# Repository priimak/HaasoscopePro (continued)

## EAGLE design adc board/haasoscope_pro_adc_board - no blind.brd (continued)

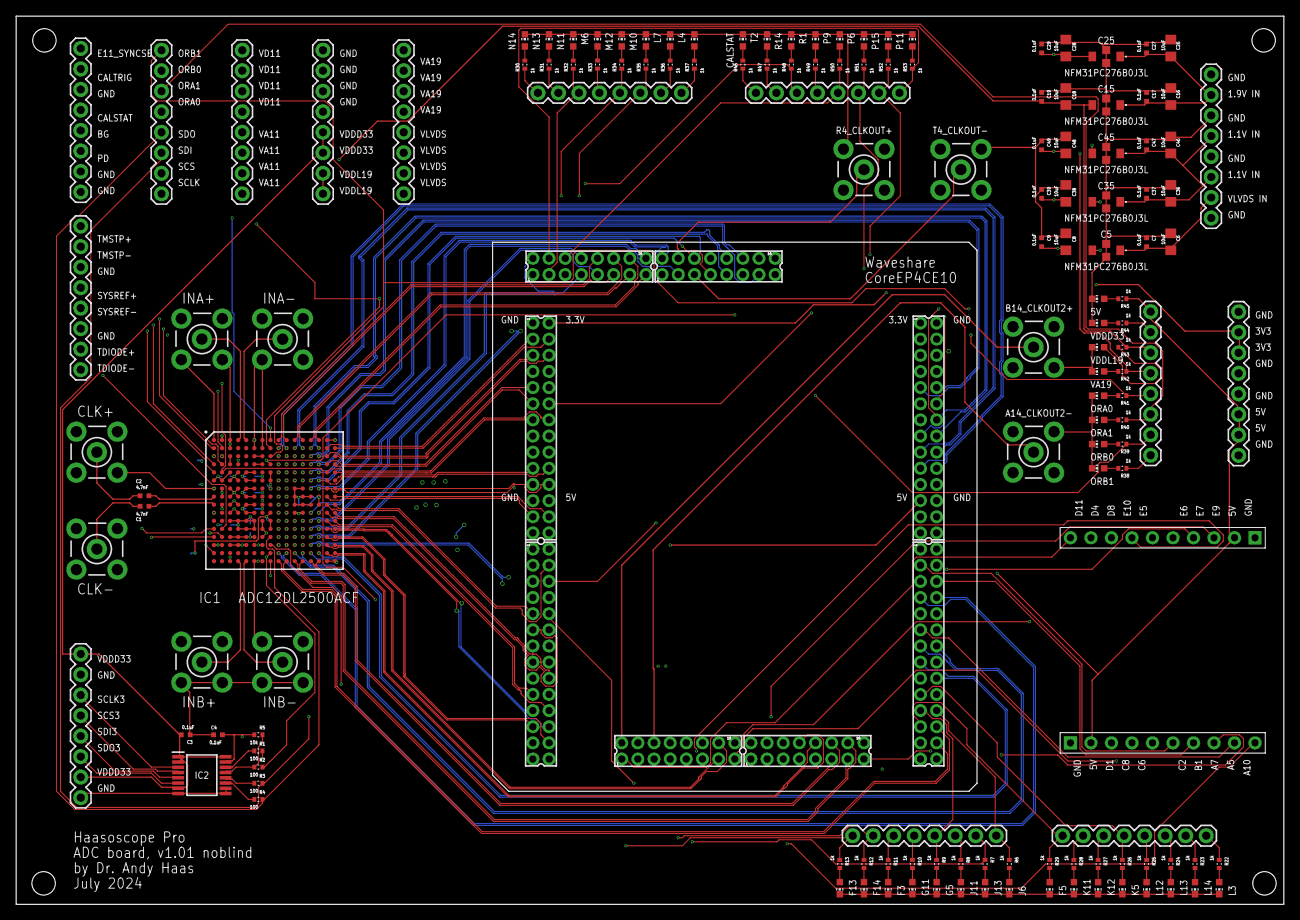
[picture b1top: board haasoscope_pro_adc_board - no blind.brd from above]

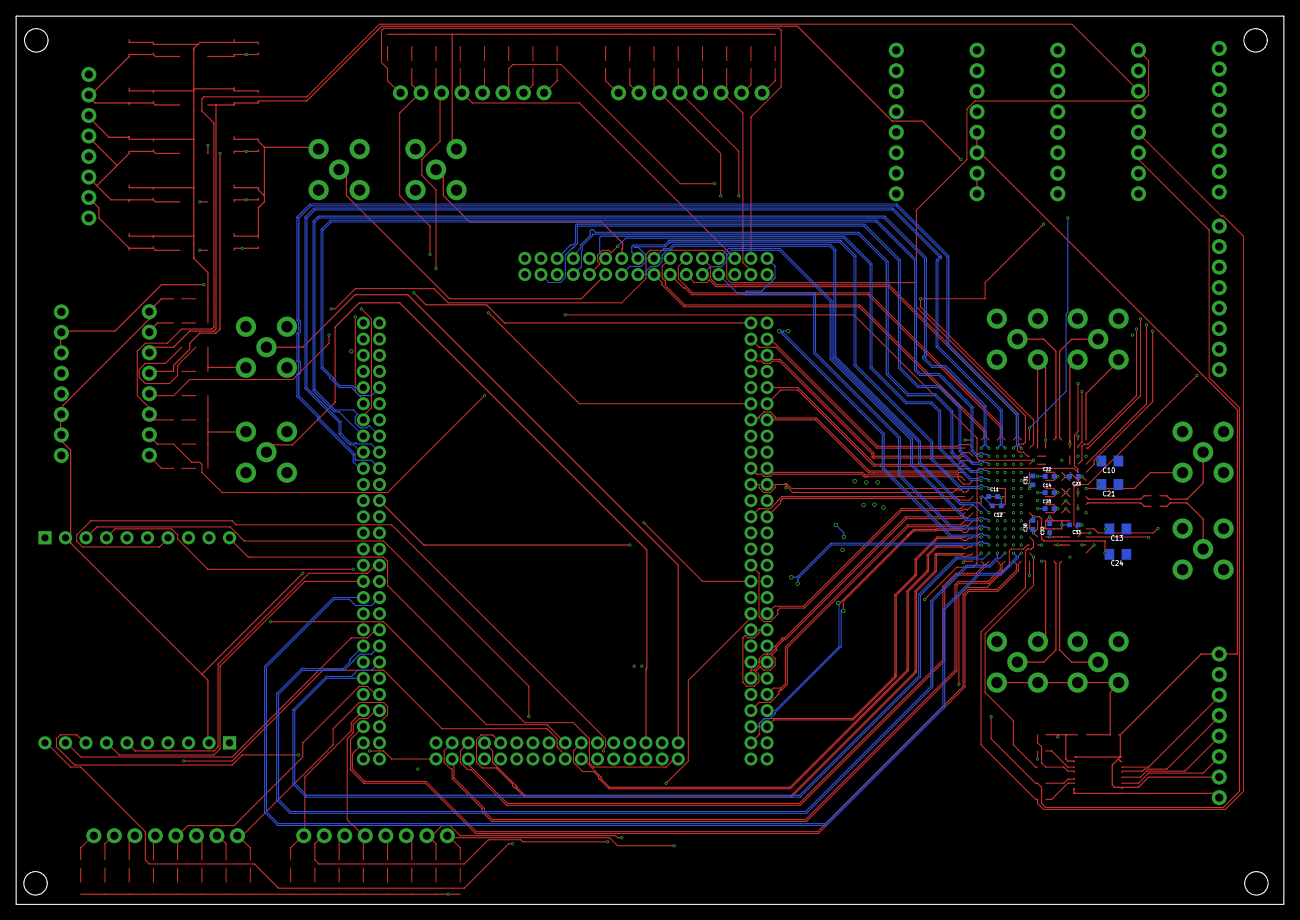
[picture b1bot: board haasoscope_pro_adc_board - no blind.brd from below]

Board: 10 copper layers, 157.0 x 110.0 mm, 164 parts (14 on the bottom side), 250 nets.

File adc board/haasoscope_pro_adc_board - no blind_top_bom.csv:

Comment,Designator,Footprint,LCSC Part #
0.1uF,C3 C4 C7 C9 C17 C19 C27 C29 C37 C39 C47 C49,RESC0402_N,
1k,R6 R7 R8 R9 R10 R11 R12 R13 R22 R23 R24 R25 R26 R27 R28 R29 R30 R31 R32 R33 R34 R35 R36 R37 R38 R39 R40 R41 R42 R43 R44 R45 R46 R47 R48 R49 R50 R51 R52 R53,RES-0402,
4.7nF,C1 C2,RESC0402_N,
10k,R5,RES-0402,
10uF,C6 C8 C16 C18 C26 C28 C36 C38 C46 C48,RESC0805_N,
100,R1 R2 R3 R4,RES-0402,
ADC12DL2500ACF,IC1,BGA256C100P16X16_1700X1700X331,
NFM31PC276B0J3L,C5 C15 C25 C35 C45,NFM31HK103R1H3L,
SN74AVC4T774PWR,IC2,SOP65P640X120-16N,
red,LED1 LED2 LED3 LED4 LED5 LED6 LED7 LED8 LED17 LED18 LED19 LED20 LED21 LED22 LED23 LED24 LED25 LED26 LED27 LED28 LED29 LED30 LED31 LED32 LED33 LED34 LED35 LED36 LED37 LED38 LED39 LED40 LED41 LED42 LED43 LED44 LED45 LED46 LED47 LED48,CHIP-LED0603,

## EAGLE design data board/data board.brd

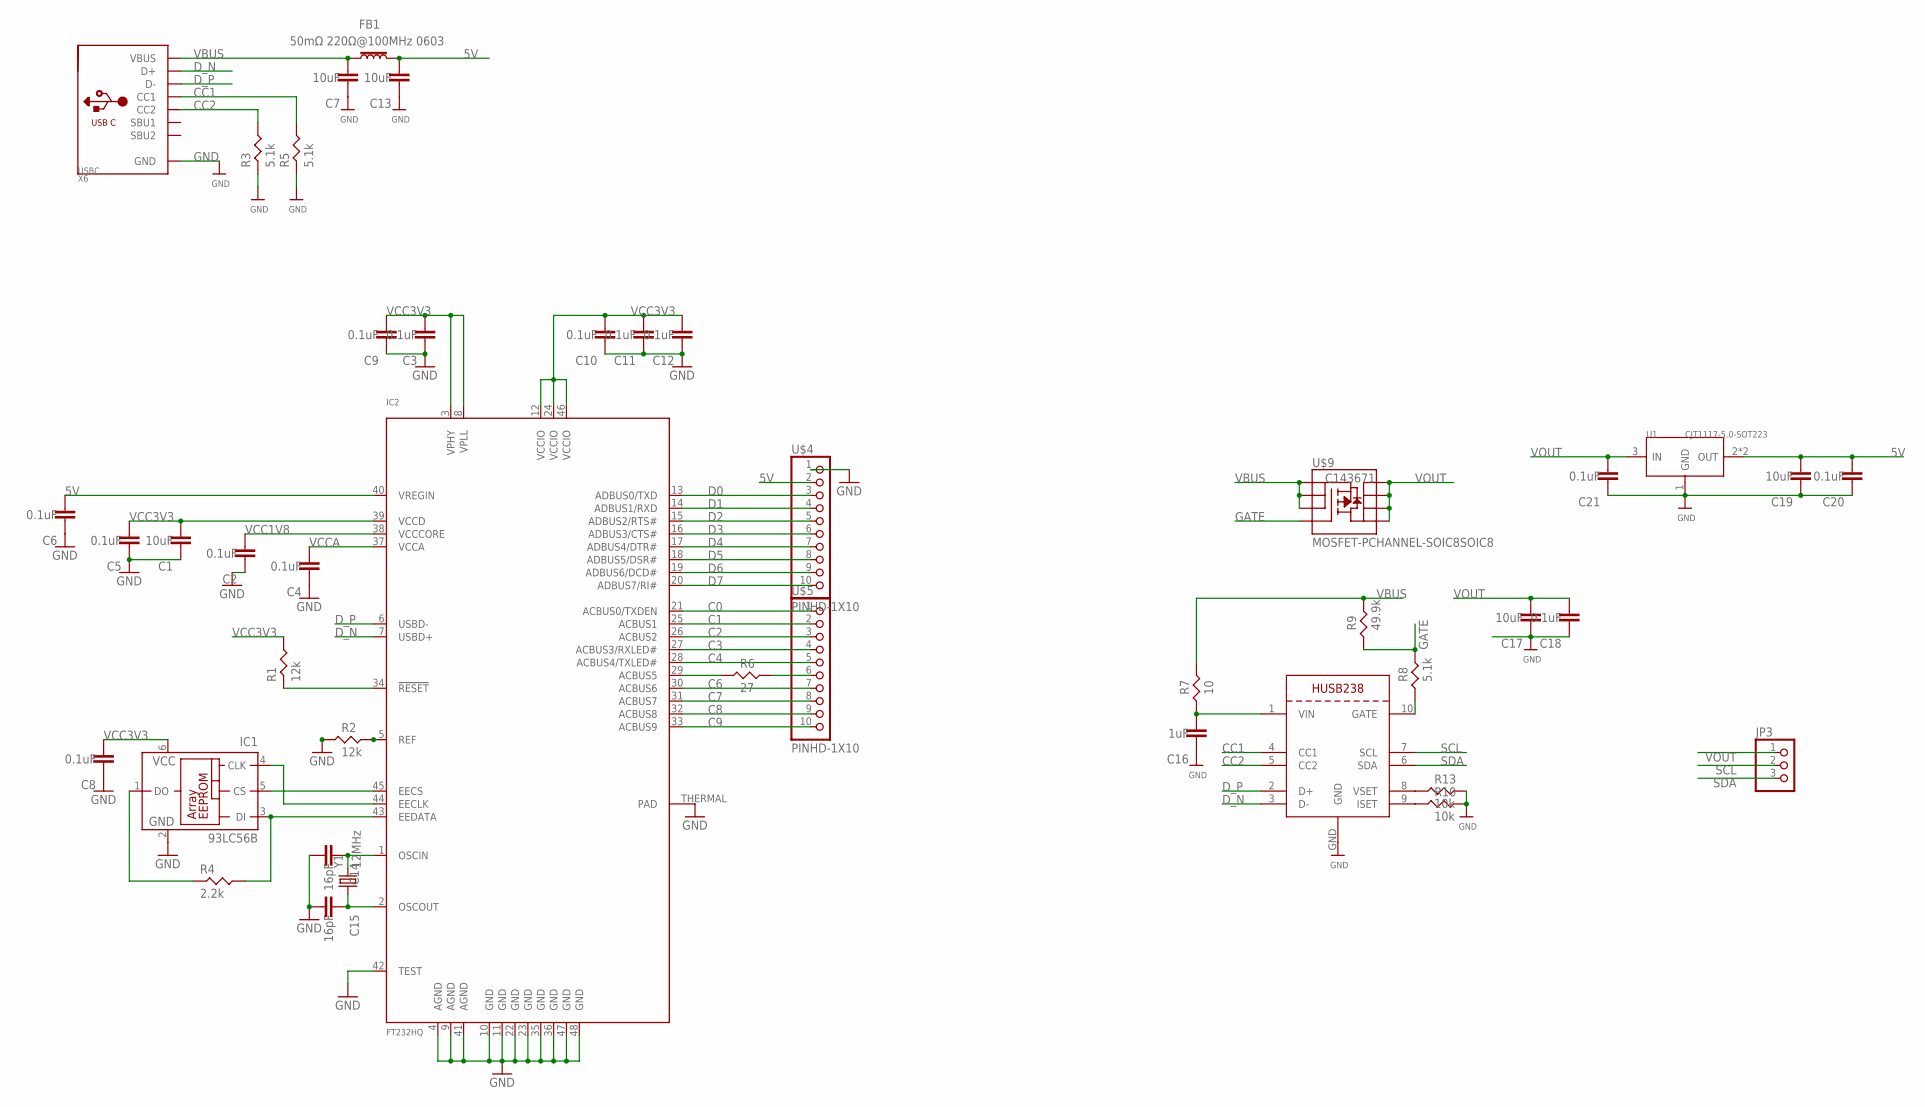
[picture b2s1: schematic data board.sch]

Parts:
C1, C7, C13, C17, C19: 10uF; RESC0805_N
C2, C3, C4, C5, C6, C8, C9, C10, C11, C12, C18, C20, C21: 0.1uF; RESC0402_N
C14, C15: 16pF; RESC0402_N
C16: 1uF; RESC0402_N
FB1: 50mΩ 220Ω@100MHz 0603; 0603
IC1: 93LC56B; SOT23-6
IC2: FT232HQ; QFN48_8MM
JP3: HEADER-1X3ROUND; 1X03_ROUND
R1, R2: 12k; RES-0402
R3, R5, R8: 5.1k; RES-0402
R4: 2.2k; RES-0402
R6: 27; RES-0402
R7: 10; RES-0402
R9: 49.9k; RES-0402
R10, R13: 10k; RES-0402
U1: CJT1117-5.0-SOT223; SOT-223
U$4, U$5: PINHD-1X10; 1X10-BIG
U$9: MOSFET-PCHANNEL-SOIC8SOIC8; SO08; LCSC C143671
X3: HUSB238; DFN10_3X3MM
X6: USBC; USB_C_CUSB31-CFM2AX-01-X
Y1: 12MHz; CRYSTAL-SMD-5X3; LCSC C2901628

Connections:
5V: C6.2, C13.2, C19.2, C20.2, FB1.2, IC2.40 (VREGIN), U1.2 (OUT), U1.TER (OUT), U$4.2
C0: IC2.21 (ACBUS0/TXDEN), U$5.1
C1: IC2.25 (ACBUS1), U$5.2
C2: IC2.26 (ACBUS2), U$5.3
C3: IC2.27 (ACBUS3/RXLED#), U$5.4
C4: IC2.28 (ACBUS4/TXLED#), U$5.5
C6: IC2.30 (ACBUS6), U$5.7
C7: IC2.31 (ACBUS7), U$5.8
C8: IC2.32 (ACBUS8), U$5.9
C9: IC2.33 (ACBUS9), U$5.10
CC1: R5.P$2, X3.4 (CC1), X6.A5 (CC1)
CC2: R3.P$2, X3.5 (CC2), X6.B5 (CC2)
D0: IC2.13 (ADBUS0/TXD), U$4.3
D1: IC2.14 (ADBUS1/RXD), U$4.4
D2: IC2.15 (ADBUS2/RTS#), U$4.5
D3: IC2.16 (ADBUS3/CTS#), U$4.6
D4: IC2.17 (ADBUS4/DTR#), U$4.7
D5: IC2.18 (ADBUS5/DSR#), U$4.8
D6: IC2.19 (ADBUS6/DCD#), U$4.9
D7: IC2.20 (ADBUS7/RI#), U$4.10
D_N: IC2.7 (USBD+), X3.3 (D-), X6.A6 (D+), X6.B6 (D+)
D_P: IC2.6 (USBD-), X3.2 (D+), X6.A7 (D-), X6.B7 (D-)
GATE: R8.P$2, R9.P$1, U$9.4 (G)
GND: C1.1, C2.1, C3.1, C4.1, C5.1, C6.1, C7.1, C8.1, C9.1, C10.1, C11.1, C12.1, C13.1, C14.2, C15.2, C16.1, C17.1, C18.1, C19.1, C20.1, C21.1, IC1.2 (GND), IC2.4 (AGND), IC2.9 (AGND), IC2.10 (GND), IC2.11 (GND), IC2.22 (GND), IC2.23 (GND), IC2.35 (GND), IC2.36 (GND), IC2.41 (AGND), IC2.42 (TEST), IC2.47 (GND), IC2.48 (GND), IC2.THERMAL (PAD), R2.P$1, R3.P$1, R5.P$1, R10.P$2, R13.P$2, U1.1 (GND), U$4.1, X3.GND, X6.A1B12 (GND), X6.B1A12 (GND)
unnamed: IC2.5 (REF), R2.P$2
unnamed: C14.1, IC2.1 (OSCIN), Y1.3 (2)
unnamed: C15.1, IC2.2 (OSCOUT), Y1.1
unnamed: IC2.29 (ACBUS5), R6.P$1
unnamed: R6.P$2, U$5.6
unnamed: C16.2, R7.P$1, X3.1 (VIN)
unnamed: IC2.34 (!RESET), R1.P$1
unnamed: R8.P$1, X3.10 (GATE)
unnamed: IC1.3 (DI), IC2.43 (EEDATA), R4.P$2
unnamed: IC1.5 (CS), IC2.45 (EECS)
unnamed: IC1.4 (CLK), IC2.44 (EECLK)
unnamed: IC1.1 (DO), R4.P$1
unnamed: R13.P$1, X3.8 (VSET)
unnamed: R10.P$1, X3.9 (ISET)
SCL: JP3.2, X3.7 (SCL)
SDA: JP3.3, X3.6 (SDA)
VBUS: C7.2, FB1.1, R7.P$2, R9.P$2, U$9.1 (S), U$9.2 (S), U$9.3 (S), X6.A4B9 (VBUS), X6.B4A9 (VBUS)
VCC1V8: C2.2, IC2.38 (VCCCORE)
VCC3V3: C1.2, C3.2, C5.2, C8.2, C9.2, C10.2, C11.2, C12.2, IC1.6 (VCC), IC2.3 (VPHY), IC2.8 (VPLL), IC2.12 (VCCIO), IC2.24 (VCCIO), IC2.39 (VCCD), IC2.46 (VCCIO), R1.P$2
VCCA: C4.2, IC2.37 (VCCA)
VOUT: C17.2, C18.2, C21.2, JP3.1, U1.3 (IN), U$9.5 (D), U$9.6 (D), U$9.7 (D), U$9.8 (D)

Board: 4 copper layers, 43 parts (0 on the bottom side), 45 nets, no tracks yet.

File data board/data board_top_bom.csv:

Comment,Designator,Footprint,LCSC Part #
0.1uF,C2 C3 C4 C5 C6 C8 C9 C10 C11 C12 C18 C20 C21,RESC0402_N,
1uF,C16,RESC0402_N,
2.2k,R4,RES-0402,
5.1k,R8,RES-0402,
10,R7,RES-0402,
10k,R10 R13,RES-0402,
10uF,C1 C7 C13 C17 C19,RESC0805_N,
12MHz,Y1,CRYSTAL-SMD-5X3,C2901628
12k,R1 R2,RES-0402,
16pF,C14 C15,RESC0402_N,
27,R6,RES-0402,
49.9k,R9,RES-0402,
50mΩ 220Ω@100MHz 0603,FB1,0603,C710364
93LC56B,IC1,SOT23-6,
CJT1117-5.0-SOT223,U1,SOT-223,
FT232HQ,IC2,QFN48_8MM,
HUSB238,X3,DFN10_3X3MM,
MOSFET-PCHANNEL-SOIC8SOIC8,U$9,SO08,C143671
USBC,X6,USB_C_CUSB31-CFM2AX-01-X,C5307756

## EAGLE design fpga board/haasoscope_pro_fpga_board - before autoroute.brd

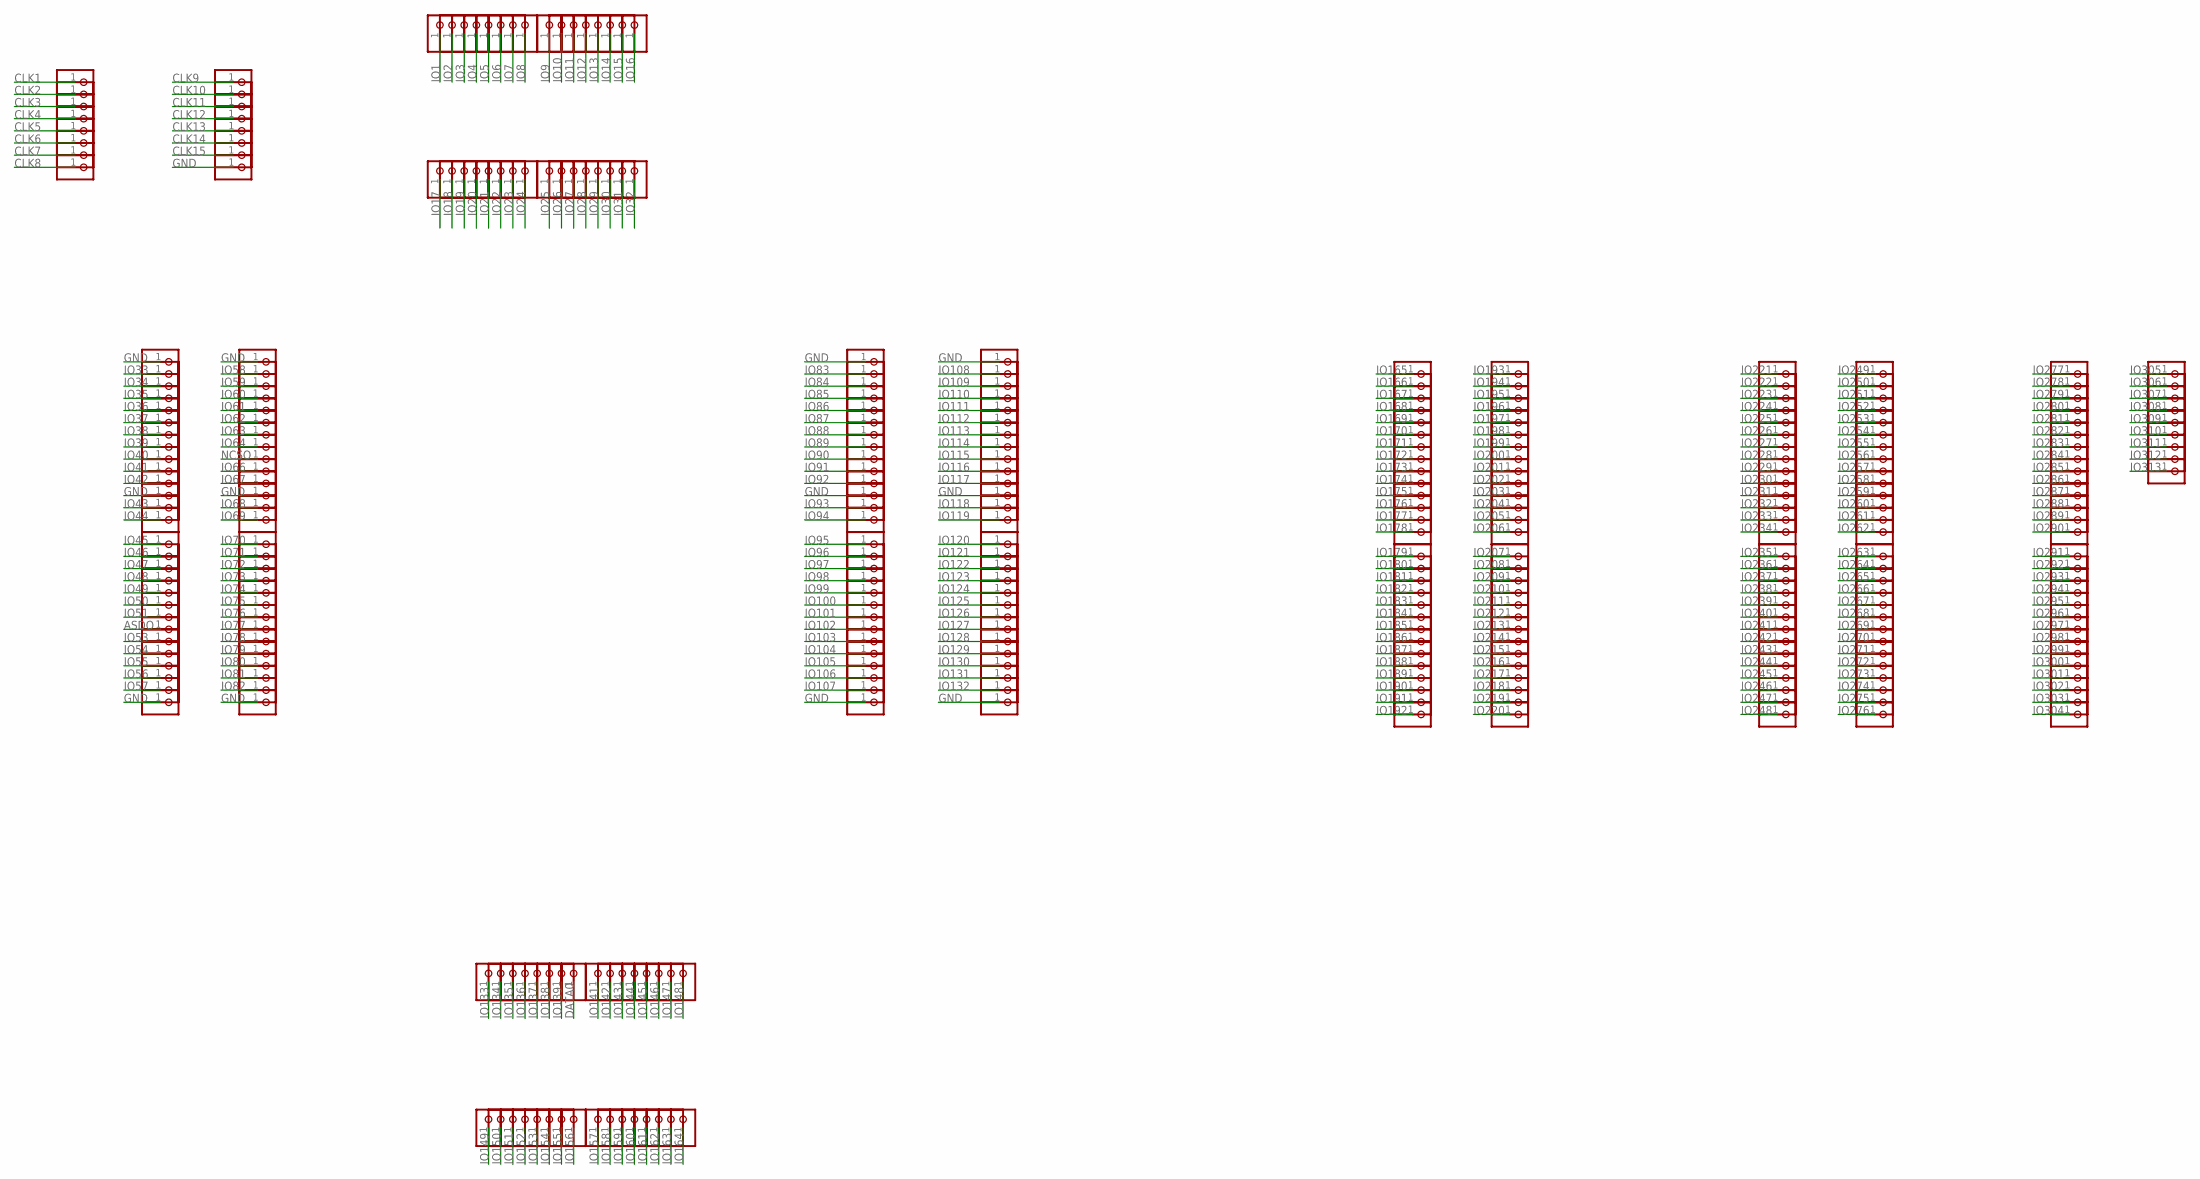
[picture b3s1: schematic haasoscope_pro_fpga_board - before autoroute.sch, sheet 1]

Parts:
JP1, JP2, JP4, JP5, JP6, JP7, JP8, JP9, JP10, JP11, JP12, JP13, JP14, JP15, JP16, JP17, JP18, JP19, JP20, JP21, JP22, JP23, JP24, JP25, JP26, JP27, JP28, JP29, JP30, JP31, JP32, JP33, JP34, JP35, JP36, JP37, JP38, JP39, JP40, JP41, JP42, JP43, JP44, JP45, JP46, JP47, JP48, JP49, JP50, JP51, JP52, JP53, JP54, JP55, JP56, JP57, JP58, JP59, JP60, JP61, JP62, JP63, JP64, JP65, JP66, JP67, JP68, JP69, JP70, JP71, JP72, JP73, JP74, JP75, JP76, JP77, JP78, JP79, JP80, JP81, JP82, JP83, JP84, JP85, JP86, JP87, JP88, JP89, JP90, JP91, JP92, JP93, JP94, JP95, JP96, JP97, JP98, JP99, JP100, JP101, JP102, JP103, JP104, JP105, JP106, JP107, JP108, JP109, JP110, JP111, JP112, JP113, JP114, JP115, JP116, JP117, JP118, JP119, JP120, JP121, JP122, JP123, JP124, JP125, JP126, JP127, JP128, JP129, JP130, JP131, JP132, JP133, JP134, JP135, JP136, JP137, JP138, JP139, JP140, JP141, JP142, JP143, JP144, JP145, JP146, JP147, JP148, JP149, JP150, JP151, JP152, JP153, JP154, JP155, JP156, JP157, JP158, JP159, JP160, JP161, JP162, JP163, JP164, JP165, JP166, JP167, JP168, JP169, JP170, JP171, JP172, JP173, JP174, JP175, JP176, JP177, JP178, JP179, JP180, JP181, JP182, JP183, JP184, JP185, JP186, JP187, JP188, JP189, JP190, JP191, JP192, JP193, JP194, JP195, JP196, JP197, JP198, JP199, JP200, JP201, JP202, JP203, JP204, JP205, JP206, JP207, JP208, JP209, JP210, JP211, JP212, JP213, JP214, JP215, JP216, JP217, JP218, JP219, JP220, JP221, JP222, JP223, JP224, JP225, JP226, JP227, JP228, JP229, JP230, JP231, JP232, JP233, JP234, JP235, JP236, JP237, JP238, JP239, JP240, JP241, JP242, JP243, JP244, JP245, JP246, JP247, JP248, JP249, JP250, JP251, JP252, JP253, JP254, JP255, JP256, JP257, JP258, JP259, JP260, JP261, JP262, JP263, JP264, JP265, JP266, JP267, JP268, JP269, JP270, JP271, JP272, JP273, JP274, JP275, JP276, JP277, JP278, JP279, JP280, JP281, JP282, JP283, JP284, JP285, JP286, JP287, JP288, JP289, JP290, JP291, JP292, JP293, JP294, JP295, JP296, JP297, JP298, JP299, JP300, JP301, JP302, JP303, JP304, JP305, JP306, JP307, JP308, JP309, JP310, JP311, JP312, JP313, JP314, JP315, JP316, JP317, JP318, JP319, JP320, JP321, JP322, JP323, JP324, JP325, JP326, JP327, JP328, JP329, JP330, JP331, JP332, JP333, JP334, JP335, JP336, JP337, JP338, JP339, JP340, JP341, JP342: 1; 1X01

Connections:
ASDO: JP39.1; also elsewhere on the board
CLK1: JP16.1; also elsewhere on the board
CLK2: JP18.1; also elsewhere on the board
CLK3: JP17.1; also elsewhere on the board
CLK4: JP19.1; also elsewhere on the board
CLK5: JP20.1; also elsewhere on the board
CLK6: JP22.1; also elsewhere on the board
CLK7: JP21.1; also elsewhere on the board
CLK8: JP23.1; also elsewhere on the board
CLK9: JP24.1; also elsewhere on the board
CLK10: JP26.1; also elsewhere on the board
CLK11: JP25.1; also elsewhere on the board
CLK12: JP27.1; also elsewhere on the board
CLK13: JP28.1; also elsewhere on the board
CLK14: JP30.1; also elsewhere on the board
CLK15: JP29.1; also elsewhere on the board
DATA0: JP113.1; also elsewhere on the board
GND: JP1.1, JP13.1, JP31.1, JP45.1, JP46.1, JP57.1, JP73.1, JP138.1, JP149.1, JP165.1, JP166.1, JP177.1, JP193.1; also elsewhere on the board
IO1: JP74.1; also elsewhere on the board
IO2: JP76.1; also elsewhere on the board
IO3: JP75.1; also elsewhere on the board
IO4: JP77.1; also elsewhere on the board
IO5: JP78.1; also elsewhere on the board
IO6: JP80.1; also elsewhere on the board
IO7: JP79.1; also elsewhere on the board
IO8: JP81.1; also elsewhere on the board
IO9: JP82.1; also elsewhere on the board
IO10: JP84.1; also elsewhere on the board
IO11: JP83.1; also elsewhere on the board
IO12: JP85.1; also elsewhere on the board
IO13: JP86.1; also elsewhere on the board
IO14: JP88.1; also elsewhere on the board
IO15: JP87.1; also elsewhere on the board
IO16: JP89.1; also elsewhere on the board
IO17: JP90.1; also elsewhere on the board
IO18: JP92.1; also elsewhere on the board
IO19: JP91.1; also elsewhere on the board
IO20: JP93.1; also elsewhere on the board
IO21: JP94.1; also elsewhere on the board
IO22: JP96.1; also elsewhere on the board
IO23: JP95.1; also elsewhere on the board
IO24: JP97.1; also elsewhere on the board
IO25: JP98.1; also elsewhere on the board
IO26: JP100.1; also elsewhere on the board
IO27: JP99.1; also elsewhere on the board
IO28: JP101.1; also elsewhere on the board
IO29: JP102.1; also elsewhere on the board
IO30: JP104.1; also elsewhere on the board
IO31: JP103.1; also elsewhere on the board
IO32: JP105.1; also elsewhere on the board
IO33: JP4.1; also elsewhere on the board
IO34: JP2.1; also elsewhere on the board
IO35: JP5.1; also elsewhere on the board
IO36: JP6.1; also elsewhere on the board
IO37: JP8.1; also elsewhere on the board
IO38: JP7.1; also elsewhere on the board
IO39: JP9.1; also elsewhere on the board
IO40: JP10.1; also elsewhere on the board
IO41: JP12.1; also elsewhere on the board
IO42: JP11.1; also elsewhere on the board
IO43: JP14.1; also elsewhere on the board
IO44: JP15.1; also elsewhere on the board
IO45: JP32.1; also elsewhere on the board
IO46: JP34.1; also elsewhere on the board
IO47: JP33.1; also elsewhere on the board
IO48: JP35.1; also elsewhere on the board
IO49: JP36.1; also elsewhere on the board
IO50: JP38.1; also elsewhere on the board
IO51: JP37.1; also elsewhere on the board
IO53: JP40.1; also elsewhere on the board
IO54: JP42.1; also elsewhere on the board
IO55: JP41.1; also elsewhere on the board
IO56: JP43.1; also elsewhere on the board
IO57: JP44.1; also elsewhere on the board
IO58: JP48.1; also elsewhere on the board
IO59: JP47.1; also elsewhere on the board
IO60: JP49.1; also elsewhere on the board
IO61: JP50.1; also elsewhere on the board
IO62: JP52.1; also elsewhere on the board
IO63: JP51.1; also elsewhere on the board
IO64: JP53.1; also elsewhere on the board
IO66: JP56.1; also elsewhere on the board
IO67: JP55.1; also elsewhere on the board
IO68: JP58.1; also elsewhere on the board
IO69: JP59.1; also elsewhere on the board
IO70: JP60.1; also elsewhere on the board
IO71: JP62.1; also elsewhere on the board
IO72: JP61.1; also elsewhere on the board
IO73: JP63.1; also elsewhere on the board
IO74: JP64.1; also elsewhere on the board
IO75: JP66.1; also elsewhere on the board
IO76: JP65.1; also elsewhere on the board
IO77: JP67.1; also elsewhere on the board
IO78: JP68.1; also elsewhere on the board
IO79: JP70.1; also elsewhere on the board
IO80: JP69.1; also elsewhere on the board
IO81: JP71.1; also elsewhere on the board
IO82: JP72.1; also elsewhere on the board
IO83: JP140.1; also elsewhere on the board
IO84: JP139.1; also elsewhere on the board
IO85: JP141.1; also elsewhere on the board
IO86: JP142.1; also elsewhere on the board
IO87: JP144.1; also elsewhere on the board
IO88: JP143.1; also elsewhere on the board
IO89: JP145.1; also elsewhere on the board
IO90: JP146.1; also elsewhere on the board
IO91: JP148.1; also elsewhere on the board
IO92: JP147.1; also elsewhere on the board
IO93: JP150.1; also elsewhere on the board
IO94: JP151.1; also elsewhere on the board
IO95: JP152.1; also elsewhere on the board
IO96: JP154.1; also elsewhere on the board
IO97: JP153.1; also elsewhere on the board
IO98: JP155.1; also elsewhere on the board
IO99: JP156.1; also elsewhere on the board
IO100: JP158.1; also elsewhere on the board
IO101: JP157.1; also elsewhere on the board
IO102: JP159.1; also elsewhere on the board
IO103: JP160.1; also elsewhere on the board
IO104: JP162.1; also elsewhere on the board
IO105: JP161.1; also elsewhere on the board
IO106: JP163.1; also elsewhere on the board
IO107: JP164.1; also elsewhere on the board
IO108: JP168.1; also elsewhere on the board
IO109: JP167.1; also elsewhere on the board
IO110: JP169.1; also elsewhere on the board
IO111: JP170.1; also elsewhere on the board
IO112: JP172.1; also elsewhere on the board
IO113: JP171.1; also elsewhere on the board
IO114: JP173.1; also elsewhere on the board
IO115: JP174.1; also elsewhere on the board
IO116: JP176.1; also elsewhere on the board
IO117: JP175.1; also elsewhere on the board
IO118: JP178.1; also elsewhere on the board
IO119: JP179.1; also elsewhere on the board
IO120: JP180.1; also elsewhere on the board
IO121: JP182.1; also elsewhere on the board
IO122: JP181.1; also elsewhere on the board
IO123: JP183.1; also elsewhere on the board
IO124: JP184.1; also elsewhere on the board
IO125: JP186.1; also elsewhere on the board
IO126: JP185.1; also elsewhere on the board
IO127: JP187.1; also elsewhere on the board
IO128: JP188.1; also elsewhere on the board
IO129: JP190.1; also elsewhere on the board
IO130: JP189.1; also elsewhere on the board
IO131: JP191.1; also elsewhere on the board
IO132: JP192.1; also elsewhere on the board
IO133: JP106.1; also elsewhere on the board
IO134: JP108.1; also elsewhere on the board
IO135: JP107.1; also elsewhere on the board
IO136: JP109.1; also elsewhere on the board
IO137: JP110.1; also elsewhere on the board
IO138: JP112.1; also elsewhere on the board
IO139: JP111.1; also elsewhere on the board
IO141: JP114.1; also elsewhere on the board
IO142: JP116.1; also elsewhere on the board
IO143: JP115.1; also elsewhere on the board
IO144: JP117.1; also elsewhere on the board
IO145: JP118.1; also elsewhere on the board
IO146: JP120.1; also elsewhere on the board
IO147: JP119.1; also elsewhere on the board
IO148: JP121.1; also elsewhere on the board
IO149: JP122.1; also elsewhere on the board
IO150: JP124.1; also elsewhere on the board
IO151: JP123.1; also elsewhere on the board
IO152: JP125.1; also elsewhere on the board
IO153: JP126.1; also elsewhere on the board
IO154: JP128.1; also elsewhere on the board
IO155: JP127.1; also elsewhere on the board
IO156: JP129.1; also elsewhere on the board
IO157: JP130.1; also elsewhere on the board
IO158: JP132.1; also elsewhere on the board
IO159: JP131.1; also elsewhere on the board
IO160: JP133.1; also elsewhere on the board
IO161: JP134.1; also elsewhere on the board
IO162: JP136.1; also elsewhere on the board
IO163: JP135.1; also elsewhere on the board
IO164: JP137.1; also elsewhere on the board
IO165: JP194.1; also elsewhere on the board
IO166: JP196.1; also elsewhere on the board
IO167: JP195.1; also elsewhere on the board
IO168: JP197.1; also elsewhere on the board
IO169: JP198.1; also elsewhere on the board
IO170: JP200.1; also elsewhere on the board
IO171: JP199.1; also elsewhere on the board
IO172: JP201.1; also elsewhere on the board
IO173: JP202.1; also elsewhere on the board
IO174: JP204.1; also elsewhere on the board
IO175: JP203.1; also elsewhere on the board
IO176: JP205.1; also elsewhere on the board
IO177: JP206.1; also elsewhere on the board
IO178: JP207.1; also elsewhere on the board
IO179: JP208.1; also elsewhere on the board
IO180: JP210.1; also elsewhere on the board
IO181: JP209.1; also elsewhere on the board
IO182: JP211.1; also elsewhere on the board
IO183: JP212.1; also elsewhere on the board
IO184: JP214.1; also elsewhere on the board
IO185: JP213.1; also elsewhere on the board
IO186: JP215.1; also elsewhere on the board
IO187: JP216.1; also elsewhere on the board
IO188: JP218.1; also elsewhere on the board
IO189: JP217.1; also elsewhere on the board
IO190: JP219.1; also elsewhere on the board
IO191: JP220.1; also elsewhere on the board
IO192: JP221.1; also elsewhere on the board
IO193: JP222.1; also elsewhere on the board
IO194: JP224.1; also elsewhere on the board
IO195: JP223.1; also elsewhere on the board
IO196: JP225.1; also elsewhere on the board
IO197: JP226.1; also elsewhere on the board
IO198: JP228.1; also elsewhere on the board
IO199: JP227.1; also elsewhere on the board
IO200: JP229.1; also elsewhere on the board
IO201: JP230.1; also elsewhere on the board
IO202: JP232.1; also elsewhere on the board
IO203: JP231.1; also elsewhere on the board
IO204: JP233.1; also elsewhere on the board
IO205: JP234.1; also elsewhere on the board
IO206: JP235.1; also elsewhere on the board
IO207: JP236.1; also elsewhere on the board
IO208: JP238.1; also elsewhere on the board
IO209: JP237.1; also elsewhere on the board
IO210: JP239.1; also elsewhere on the board
IO211: JP240.1; also elsewhere on the board
IO212: JP242.1; also elsewhere on the board
IO213: JP241.1; also elsewhere on the board
IO214: JP243.1; also elsewhere on the board
IO215: JP244.1; also elsewhere on the board
IO216: JP246.1; also elsewhere on the board
IO217: JP245.1; also elsewhere on the board
IO218: JP247.1; also elsewhere on the board
IO219: JP248.1; also elsewhere on the board
IO220: JP249.1; also elsewhere on the board
IO221: JP250.1; also elsewhere on the board
IO222: JP252.1; also elsewhere on the board
IO223: JP251.1; also elsewhere on the board
IO224: JP253.1; also elsewhere on the board
IO225: JP254.1; also elsewhere on the board
IO226: JP256.1; also elsewhere on the board
IO227: JP255.1; also elsewhere on the board
IO228: JP257.1; also elsewhere on the board
IO229: JP258.1; also elsewhere on the board
IO230: JP260.1; also elsewhere on the board
IO231: JP259.1; also elsewhere on the board
IO232: JP261.1; also elsewhere on the board
IO233: JP262.1; also elsewhere on the board
IO234: JP263.1; also elsewhere on the board
IO235: JP264.1; also elsewhere on the board
IO236: JP266.1; also elsewhere on the board
IO237: JP265.1; also elsewhere on the board
IO238: JP267.1; also elsewhere on the board
IO239: JP268.1; also elsewhere on the board
IO240: JP270.1; also elsewhere on the board
IO241: JP269.1; also elsewhere on the board
IO242: JP271.1; also elsewhere on the board
IO243: JP272.1; also elsewhere on the board
IO244: JP274.1; also elsewhere on the board
IO245: JP273.1; also elsewhere on the board
IO246: JP275.1; also elsewhere on the board
IO247: JP276.1; also elsewhere on the board
IO248: JP277.1; also elsewhere on the board
IO249: JP278.1; also elsewhere on the board
IO250: JP280.1; also elsewhere on the board
IO251: JP279.1; also elsewhere on the board
IO252: JP281.1; also elsewhere on the board
IO253: JP282.1; also elsewhere on the board
IO254: JP284.1; also elsewhere on the board
IO255: JP283.1; also elsewhere on the board
IO256: JP285.1; also elsewhere on the board
IO257: JP286.1; also elsewhere on the board
IO258: JP288.1; also elsewhere on the board
IO259: JP287.1; also elsewhere on the board
IO260: JP289.1; also elsewhere on the board
IO261: JP290.1; also elsewhere on the board
IO262: JP291.1; also elsewhere on the board
IO263: JP292.1; also elsewhere on the board
IO264: JP294.1; also elsewhere on the board
IO265: JP293.1; also elsewhere on the board
IO266: JP295.1; also elsewhere on the board
IO267: JP296.1; also elsewhere on the board
IO268: JP298.1; also elsewhere on the board
IO269: JP297.1; also elsewhere on the board
IO270: JP299.1; also elsewhere on the board
IO271: JP300.1; also elsewhere on the board
IO272: JP302.1; also elsewhere on the board
IO273: JP301.1; also elsewhere on the board
IO274: JP303.1; also elsewhere on the board
IO275: JP304.1; also elsewhere on the board
IO276: JP305.1; also elsewhere on the board
IO277: JP306.1; also elsewhere on the board
IO278: JP308.1; also elsewhere on the board
IO279: JP307.1; also elsewhere on the board
IO280: JP309.1; also elsewhere on the board
IO281: JP310.1; also elsewhere on the board
IO282: JP312.1; also elsewhere on the board
IO283: JP311.1; also elsewhere on the board
IO284: JP313.1; also elsewhere on the board
IO285: JP314.1; also elsewhere on the board
IO286: JP316.1; also elsewhere on the board
IO287: JP315.1; also elsewhere on the board
IO288: JP317.1; also elsewhere on the board
IO289: JP318.1; also elsewhere on the board
IO290: JP319.1; also elsewhere on the board
IO291: JP320.1; also elsewhere on the board
IO292: JP322.1; also elsewhere on the board
IO293: JP321.1; also elsewhere on the board
IO294: JP323.1; also elsewhere on the board
IO295: JP324.1; also elsewhere on the board
IO296: JP326.1; also elsewhere on the board
IO297: JP325.1; also elsewhere on the board
IO298: JP327.1; also elsewhere on the board
IO299: JP328.1; also elsewhere on the board
IO300: JP330.1; also elsewhere on the board
IO301: JP329.1; also elsewhere on the board
IO302: JP331.1; also elsewhere on the board
IO303: JP332.1; also elsewhere on the board
IO304: JP333.1; also elsewhere on the board
IO305: JP334.1; also elsewhere on the board
IO306: JP336.1; also elsewhere on the board
IO307: JP335.1; also elsewhere on the board
IO308: JP337.1; also elsewhere on the board
IO309: JP338.1; also elsewhere on the board
IO310: JP340.1; also elsewhere on the board
IO311: JP339.1; also elsewhere on the board
IO312: JP341.1; also elsewhere on the board
IO313: JP342.1; also elsewhere on the board
NCSO: JP54.1; also elsewhere on the board
